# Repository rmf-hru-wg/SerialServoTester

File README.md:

Serial Servo Tester
===

シリアルサーボを動作させるための回路

* SST-Single: TTLとRS485のコネクタを1つずつ出している。KONDOのDual USBアダプターと同様にサーボの設定に使える。
* SST-SCB: 3ピンTTLのみで24ポート分生やしている。PythonなどPCからロボットを動かすための基板。

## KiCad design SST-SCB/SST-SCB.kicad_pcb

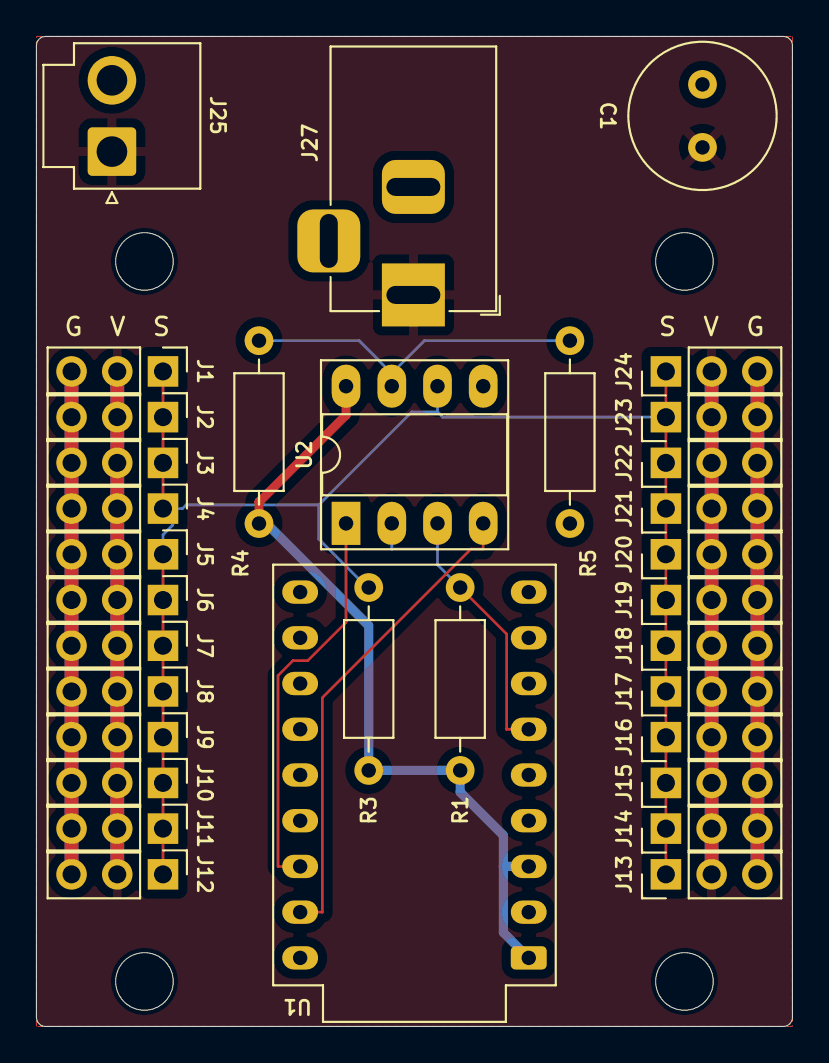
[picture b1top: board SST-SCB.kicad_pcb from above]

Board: 2 copper layers, 42.0 x 55.0 mm, 37 parts (0 on the bottom side), 8 nets.

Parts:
C1: C; C_Radial_D8.0mm_H11.5mm_P3.50mm
H1, H2, H3, H4: MountingHole; MountingHole_3.2mm_M3
J1, J2, J3, J4, J5, J6, J7, J8, J9, J10, J11, J12, J13, J14, J15, J16, J17, J18, J19, J20, J21, J22, J23, J24: Conn_01x03_Pin; PinHeader_1x03_P2.54mm_Vertical
J25: Conn_01x02_Pin; JST_VH_B2P-VH_1x02_P3.96mm_Vertical
J27: MJ-179PH; BarrelJack_Horizontal
R1, R3, R4, R5: 5.1k; R_Axial_DIN0207_L6.3mm_D2.5mm_P10.16mm_Horizontal
U1: FT231XS_Breakout; DIP-18_500_ELL
U2: LT1785AxN8; DIP-8_W7.62mm_Socket_LongPads

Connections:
/RS485A: J1.1, J2.1, J3.1, J4.1, J5.1, J6.1, J7.1, J8.1, J9.1, J10.1, J11.1, J12.1, J13.1, J14.1, J15.1, J16.1, J17.1, J18.1, J19.1, J20.1, J21.1, J22.1, J23.1, J24.1, R3.1, U2.6 (A)
/RS485B: R4.1, R5.2, U2.7 (B)
GND: C1.2, J1.3, J2.3, J3.3, J4.3, J5.3, J6.3, J7.3, J8.3, J9.3, J10.3, J11.3, J12.3, J13.3, J14.3, J15.3, J16.3, J17.3, J18.3, J19.3, J20.3, J21.3, J22.3, J23.3, J24.3, J25.2, J27.2, J27.3 (MountPin), R5.1, U1.5 (GND), U1.18 (GND), U2.5 (GND)
unnamed: R1.2, R3.2, R4.2, U1.1 (5V), U1.3 (VCCIO), U2.8 (VCC)
unnamed: R1.1, U1.6 (CBUS0), U2.2 (~RE), U2.3 (DE)
unnamed: U1.16 (RXD), U2.1 (RO)
unnamed: U1.17 (TXD), U2.4 (DI)
VCC: C1.1, J1.2, J2.2, J3.2, J4.2, J5.2, J6.2, J7.2, J8.2, J9.2, J10.2, J11.2, J12.2, J13.2, J14.2, J15.2, J16.2, J17.2, J18.2, J19.2, J20.2, J21.2, J22.2, J23.2, J24.2, J25.1, J27.1

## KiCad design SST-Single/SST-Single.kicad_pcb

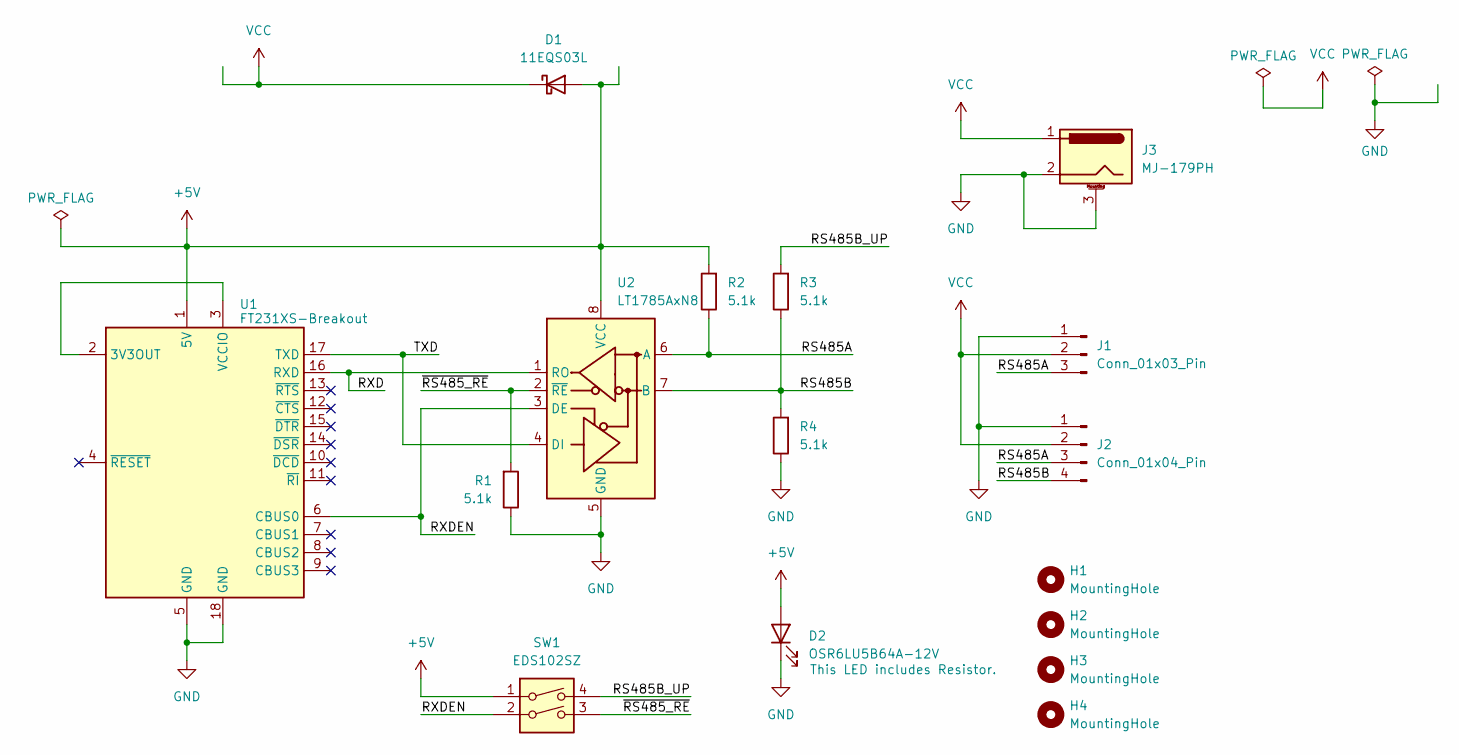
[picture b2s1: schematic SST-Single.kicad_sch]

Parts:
D1: 11EQS03L; D_T-1_P10.16mm_Horizontal
D2: OSR6LU5B64A-12V; LED_D5.0mm
H1, H2, H3, H4: MountingHole; MountingHole_3.2mm_M3
J1: Conn_01x03_Pin; PinHeader_1x03_P2.54mm_Horizontal
J2: Conn_01x04_Pin; JST_EH_S4B-EH_1x04_P2.50mm_Horizontal
J3: MJ-179PH; BarrelJack_Horizontal
R1, R2, R3, R4: 5.1k; R_Axial_DIN0207_L6.3mm_D2.5mm_P10.16mm_Horizontal
SW1: EDS102SZ; SW_DIP_SPSTx02_Slide_9.78x7.26mm_W7.62mm_P2.54mm
U1: FT231XS-Breakout; DIP-18_500_ELL
U2: LT1785AxN8; DIP-8_W7.62mm_Socket_LongPads

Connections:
+5V: D1.2 (A), D2.2 (A), R2.2, SW1.1, U1.1 (5V), U2.8 (VCC)
/RS485A: J1.3, J2.3, R2.1, U2.6 (A)
/RS485B: J2.4, R3.1, R4.2, U2.7 (B)
/RS485B_UP: R3.2, SW1.4
/RXD: U1.16 (RXD), U2.1 (RO)
/RXDEN: SW1.2, U1.6 (CBUS0), U2.3 (DE)
/TXD: U1.17 (TXD), U2.4 (DI)
/~RS485_RE: R1.2, SW1.3, U2.2 (~RE)
GND: D2.1 (K), J1.1, J2.1, J3.2, J3.3 (MountPin), R1.1, R4.1, U1.5 (GND), U1.18 (GND), U2.5 (GND)
unnamed: U1.2 (3V3OUT), U1.3 (VCCIO)
VCC: D1.1 (K), J1.2, J2.2, J3.1

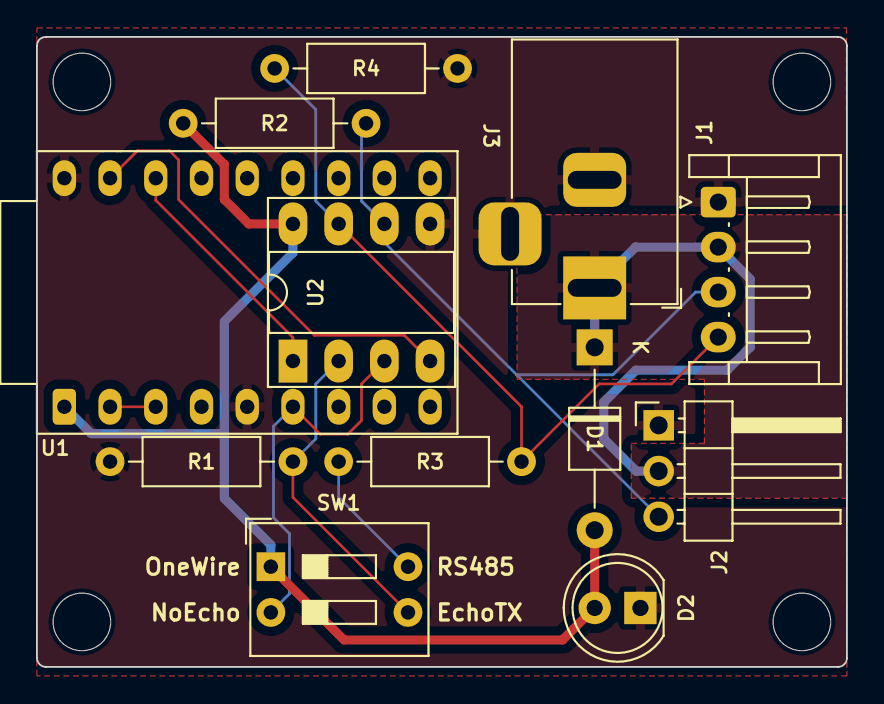
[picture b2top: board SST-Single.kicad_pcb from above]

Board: 2 copper layers, 45.0 x 35.0 mm, 16 parts (0 on the bottom side), 11 nets.

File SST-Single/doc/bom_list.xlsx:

Reference | Value | Qty | URL | Total
D1 | 11EQS03L | 1 | https://akizukidenshi.com/catalog/g/g111362/ | 1
D2 | OSR6LU5B64A-12V | 1 | https://akizukidenshi.com/catalog/g/g106250/ | 1
J1 | Conn_01x03_Pin | 1 | https://akizukidenshi.com/catalog/g/g115510/ | 1
J2 | Conn_01x04_Pin | 1 | https://www.marutsu.co.jp/pc/i/46603/ | 1
J3 | MJ-179PH | 1 | https://akizukidenshi.com/catalog/g/g106568/ | 1
R1,R2,R3,R4 | 5.1k | 4 | https://akizukidenshi.com/catalog/g/g107832/ | 4
SW1 | EDS102SZ | 1 | https://akizukidenshi.com/catalog/g/g103141/ | 1
U1 | FT231XS-Breakout | 1 | https://www.marutsu.co.jp/pc/i/1557619/ https://www.switch-science.com/products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 | 1
U2 | LT1785AxN8 | 1 | https://akizukidenshi.com/catalog/g/g115806/ | 1
 | 8PIN IC Socket | 1 | https://akizukidenshi.com/catalog/g/g100017/ | 1
Number of set | 1

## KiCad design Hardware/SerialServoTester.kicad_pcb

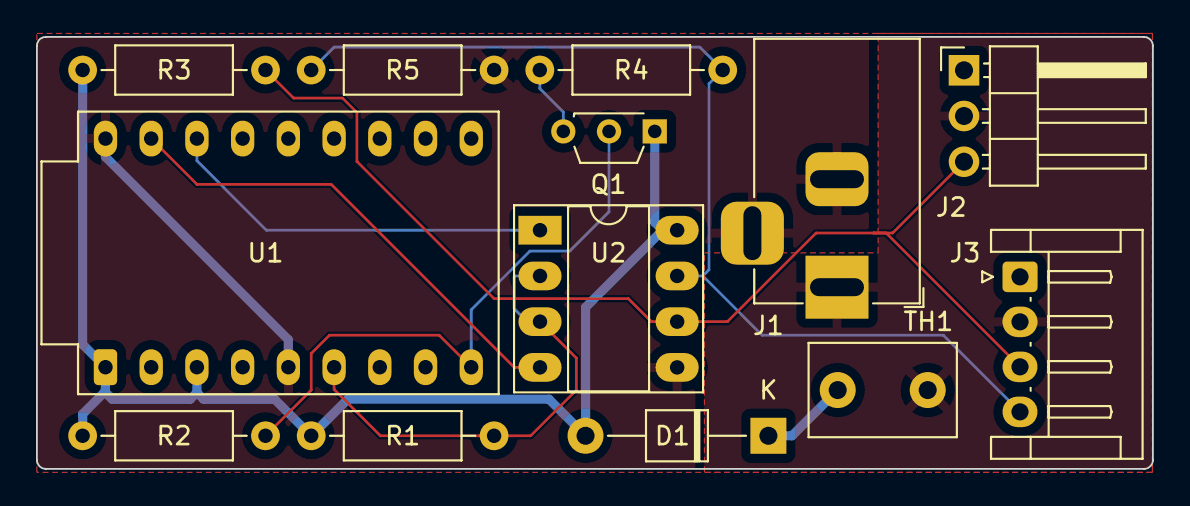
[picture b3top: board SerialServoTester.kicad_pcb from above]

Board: 2 copper layers, 62.0 x 24.0 mm, 13 parts (0 on the bottom side), 11 nets.

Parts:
D1: 11EQS03L; D_T-1_P10.16mm_Horizontal
J1: MJ-179PH; BarrelJack_Horizontal
J2: Conn_01x03_Pin; PinHeader_1x03_P2.54mm_Horizontal
J3: Conn_01x04_Pin; JST_EH_S4B-EH_1x04_P2.50mm_Horizontal
Q1: 2SJ498-D; TO-92S_Wide
R1, R2, R3, R4, R5: 5.1k; R_Axial_DIN0207_L6.3mm_D2.5mm_P10.16mm_Horizontal
TH1: PTGL07AR820M9A51B0; C_Disc_D8.0mm_W5.0mm_P5.00mm
U1: FT231XS_Breakout; DIP-18_500_ELL
U2: LT1785AxN8; DIP-8_W7.62mm_Socket_LongPads

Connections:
/RS485A: J2.3, J3.3, R3.1, U2.6 (A)
/RS485B: J3.4, R4.1, R5.2, U2.7 (B)
/~EN_4PIN: Q1.2 (G), R2.1, U1.9 (CBUS3)
GND: J1.2, J1.3 (MountPin), J2.1, J3.1, R5.1, U1.5 (GND), U1.18 (GND), U2.5 (GND)
unnamed: D1.2 (A), Q1.1 (D), R1.2, R2.2, R3.2, U1.1 (5V), U1.3 (VCCIO), U2.8 (VCC)
unnamed: D1.1 (K), TH1.2
unnamed: Q1.3 (S), R4.2
unnamed: R1.1, U1.6 (CBUS0), U2.2 (~RE), U2.3 (DE)
unnamed: U1.16 (RXD), U2.1 (RO)
unnamed: U1.17 (TXD), U2.4 (DI)
VCC: J1.1, J2.2, J3.2, TH1.1

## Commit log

2024-03-16 Baseline
2024-03-16 Update PCB data
2024-03-23 Update PCB design
2024-03-25 Move directory from Hardware to Hardware/SST-Single
2024-03-25 Copy from SST-Single to SST-SCB
2024-04-14 Update SST-Single Board
2024-04-14 Commit Serial Servo Tester for Servo Control Board
2024-04-14 Move directories
2024-04-14 Add URL test and team logo to the footprint
2024-05-08 Add DIP switch to select serial mode
2024-05-13 Remove FET and modify resistors of RS485 DE line
2024-05-13 Update parts layout
2024-05-13 Update PCB pattern
2024-05-20 Modify to order slightly
2024-05-20 Add CC-BY logo
2024-06-26 Add documents
2024-06-26 Rename README
2024-07-20 Fix PCB patterns
